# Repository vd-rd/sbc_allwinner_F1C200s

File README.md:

# Allwinner F1C200s SBC

This board embeds a SIP (single core 533MHz ARM926EJ-S with 64MB DDR) with AXP173 PMIC, IO headers and microSD/eMMC storage. The board is also compatible with the smaller F1C100s that only embedds 32MB DDR RAM.

Note: The uC has two SDIO controllers (SDIO0 - 4bit wide, SDIO1 - 1bit wide). SDIO0 is used for SDCard. To provide wireless networking, while not sacrificing a large amount of pins, a design decision was made to use ESP32 module to provide WiFi/BT capabilities connected via SPI bus, leveraging [ESP_HOSTED_NG](https://github.com/espressif/esp-hosted) as a solution.
## Board overview (draft):

[TBD]

## Board features

| Characteristic | Description |
| --- | --- |
| Dimensions | 60mm x 40mm |
| Processor | Allwinner F1C100s/F1C200s ARM926EJ-S @533MHz |
| Oscillators | 24MHz main clock |
| RAM | 32/64MB embedded DDR memory |
| Storage | microSD/eMMC |
| USB | 1 microUSB OTG |
| Supply | Power path between USB/Vin/Battery, 5V max |

## Notes and observations
[TBD]

## Resources
 - online viewer for schematic/layout (https://cadlab.io/project/23988).

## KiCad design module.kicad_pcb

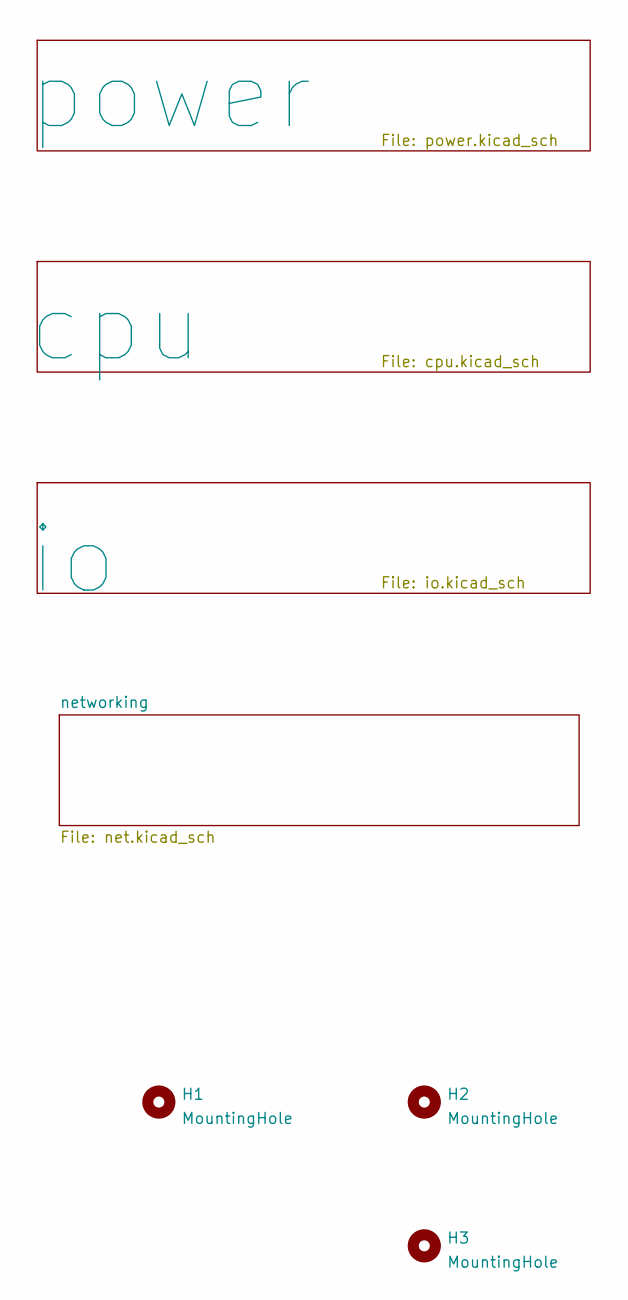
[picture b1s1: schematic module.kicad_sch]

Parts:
H1, H2, H3: MountingHole; MountingHole_2.7mm_M2.5

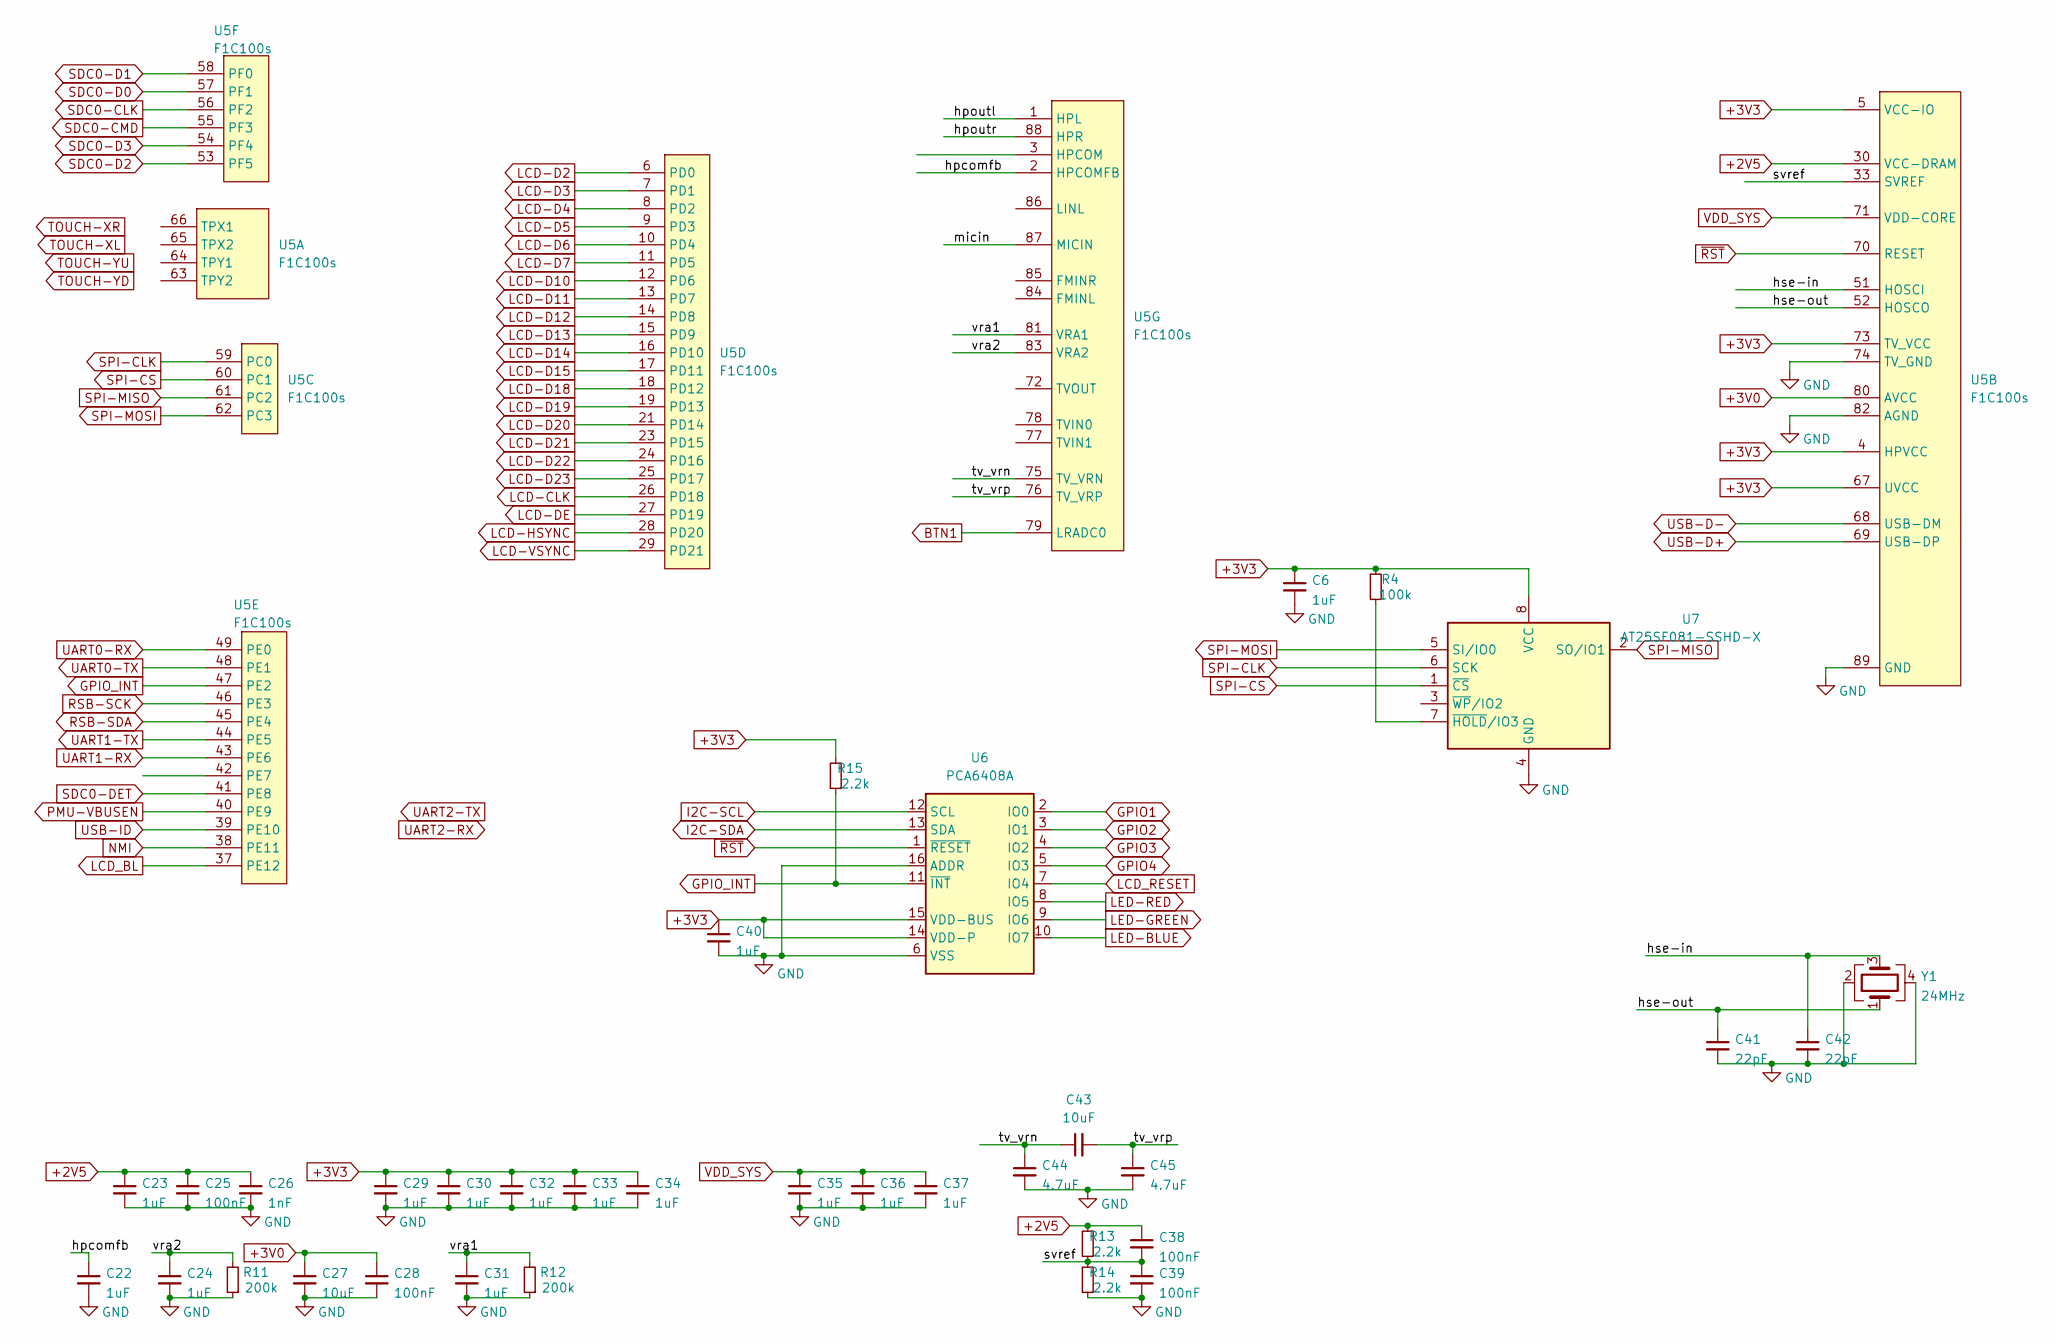
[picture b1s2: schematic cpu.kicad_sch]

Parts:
C6, C22, C23, C24, C29, C30, C31, C32, C33, C34, C35, C36, C37, C40: 1uF; C_0402_1005Metric
C25, C28, C38, C39: 100nF; C_0402_1005Metric
C26: 1nF; C_0402_1005Metric
C27, C43: 10uF; C_0603_1608Metric
C41, C42: 22pF; C_0402_1005Metric
C44, C45: 4.7uF; C_0603_1608Metric
R4: 100k; R_0402_1005Metric
R11, R12: 200k; R_0402_1005Metric
R13, R14, R15: 2.2k; R_0402_1005Metric
U5: F1C100s; QFN-88_EP_10x10_Pitch0.4mm
U6: PCA6408A; QFN-16-1EP_3x3mm_P0.5mm_EP1.7x1.7mm
U7: AT25SF081-SSHD-X; SOIC-8_3.9x4.9mm_P1.27mm
Y1: 24MHz; Crystal_SMD_3225-4Pin_3.2x2.5mm

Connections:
+2V5: C23.1, C25.1, C26.1, C38.1, R13.2, U5.30 (VCC-DRAM), U5.31 (VCC-DRAM), U5.32 (VCC-DRAM), U5.34 (VCC-DRAM), U5.36 (VCC-DRAM); also elsewhere on the board
+3V0: C27.1, C28.1, U5.80 (AVCC); also elsewhere on the board
+3V3: C6.1, C29.1, C30.1, C32.1, C33.1, C34.1, C40.1, R4.2, R15.2, U5.4 (HPVCC), U5.5 (VCC-IO), U5.20 (VCC-IO), U5.50 (VCC-IO), U5.67 (UVCC), U5.73 (TV_VCC), U6.14 (VDD-P), U6.15 (VDD-BUS), U7.8 (VCC); also elsewhere on the board
/cpu/hpcomfb: C22.1, U5.2 (HPCOMFB)
/cpu/hpoutl: U5.1 (HPL)
/cpu/hpoutr: U5.88 (HPR)
/cpu/hse-in: C42.1, U5.51 (HOSCI), Y1.3
/cpu/hse-out: C41.1, U5.52 (HOSCO), Y1.1
/cpu/micin: U5.87 (MICIN)
/cpu/svref: C38.2, C39.1, R13.1, R14.2, U5.33 (SVREF)
/cpu/tv_vrn: C43.1, C44.1, U5.75 (TV_VRN)
/cpu/tv_vrp: C43.2, C45.1, U5.76 (TV_VRP)
/cpu/vra1: C31.1, R12.2, U5.81 (VRA1)
/cpu/vra2: C24.1, R11.2, U5.83 (VRA2)
BTN1: U5.79 (LRADC0); also elsewhere on the board
GND: C6.2, C22.2, C23.2, C24.2, C25.2, C26.2, C27.2, C28.2, C29.2, C30.2, C31.2, C32.2, C33.2, C34.2, C35.2, C36.2, C37.2, C39.2, C40.2, C41.2, C42.2, C44.2, C45.2, R11.1, R12.1, R14.1, U5.74 (TV_GND), U5.82 (AGND), U5.89 (GND), U6.6 (VSS), U6.16 (ADDR), U7.4 (GND), Y1.2, Y1.4; also elsewhere on the board
GPIO1: U6.2 (IO0); also elsewhere on the board
GPIO2: U6.3 (IO1); also elsewhere on the board
GPIO3: U6.4 (IO2); also elsewhere on the board
GPIO4: U6.5 (IO3); also elsewhere on the board
GPIO_INT: R15.1, U5.47 (PE2), U6.11 (~INT)
I2C-SCL: U6.12 (SCL); also elsewhere on the board
I2C-SDA: U6.13 (SDA); also elsewhere on the board
LCD-CLK: U5.26 (PD18); also elsewhere on the board
LCD-D2: U5.6 (PD0); also elsewhere on the board
LCD-D3: U5.7 (PD1); also elsewhere on the board
LCD-D4: U5.8 (PD2); also elsewhere on the board
LCD-D5: U5.9 (PD3); also elsewhere on the board
LCD-D6: U5.10 (PD4); also elsewhere on the board
LCD-D7: U5.11 (PD5); also elsewhere on the board
LCD-D10: U5.12 (PD6); also elsewhere on the board
LCD-D11: U5.13 (PD7); also elsewhere on the board
LCD-D12: U5.14 (PD8); also elsewhere on the board
LCD-D13: U5.15 (PD9); also elsewhere on the board
LCD-D14: U5.16 (PD10); also elsewhere on the board
LCD-D15: U5.17 (PD11); also elsewhere on the board
LCD-D18: U5.18 (PD12); also elsewhere on the board
LCD-D19: U5.19 (PD13); also elsewhere on the board
LCD-D20: U5.21 (PD14); also elsewhere on the board
LCD-D21: U5.23 (PD15); also elsewhere on the board
LCD-D22: U5.24 (PD16); also elsewhere on the board
LCD-D23: U5.25 (PD17); also elsewhere on the board
LCD-DE: U5.27 (PD19); also elsewhere on the board
LCD-HSYNC: U5.28 (PD20); also elsewhere on the board
LCD-VSYNC: U5.29 (PD21); also elsewhere on the board
LCD_BL: U5.37 (PE12); also elsewhere on the board
LCD_RESET: U6.7 (IO4); also elsewhere on the board
LED-BLUE: U6.10 (IO7); also elsewhere on the board
LED-GREEN: U6.9 (IO6); also elsewhere on the board
LED-RED: U6.8 (IO5); also elsewhere on the board
NMI: U5.38 (PE11); also elsewhere on the board
unnamed: R4.1, U7.7 (~HOLD/IO3)
PMU-VBUSEN: U5.40 (PE9); also elsewhere on the board
RSB-SCK: U5.46 (PE3); also elsewhere on the board
RSB-SDA: U5.45 (PE4); also elsewhere on the board
SDC0-CLK: U5.56 (PF2); also elsewhere on the board
SDC0-CMD: U5.55 (PF3); also elsewhere on the board
SDC0-D0: U5.57 (PF1); also elsewhere on the board
SDC0-D1: U5.58 (PF0); also elsewhere on the board
SDC0-D2: U5.53 (PF5); also elsewhere on the board
SDC0-D3: U5.54 (PF4); also elsewhere on the board
SDC0-DET: U5.41 (PE8); also elsewhere on the board
SPI-CLK: U5.59 (PC0), U7.6 (SCK); also elsewhere on the board
SPI-CS: U5.60 (PC1), U7.1 (~CS); also elsewhere on the board
SPI-MISO: U5.61 (PC2), U7.2 (SO/IO1); also elsewhere on the board
SPI-MOSI: U5.62 (PC3), U7.5 (SI/IO0); also elsewhere on the board
UART0-RX: U5.49 (PE0); also elsewhere on the board
UART0-TX: U5.48 (PE1); also elsewhere on the board
UART1-RX: U5.43 (PE6); also elsewhere on the board
UART1-TX: U5.44 (PE5); also elsewhere on the board
USB-D+: U5.69 (USB-DP); also elsewhere on the board
USB-D-: U5.68 (USB-DM); also elsewhere on the board
USB-ID: U5.39 (PE10); also elsewhere on the board
VDD_SYS: C35.1, C36.1, C37.1, U5.22 (VDD-CORE), U5.35 (VDD-CORE), U5.71 (VDD-CORE); also elsewhere on the board
~RST: U5.70 (RESET), U6.1 (~RESET); also elsewhere on the board

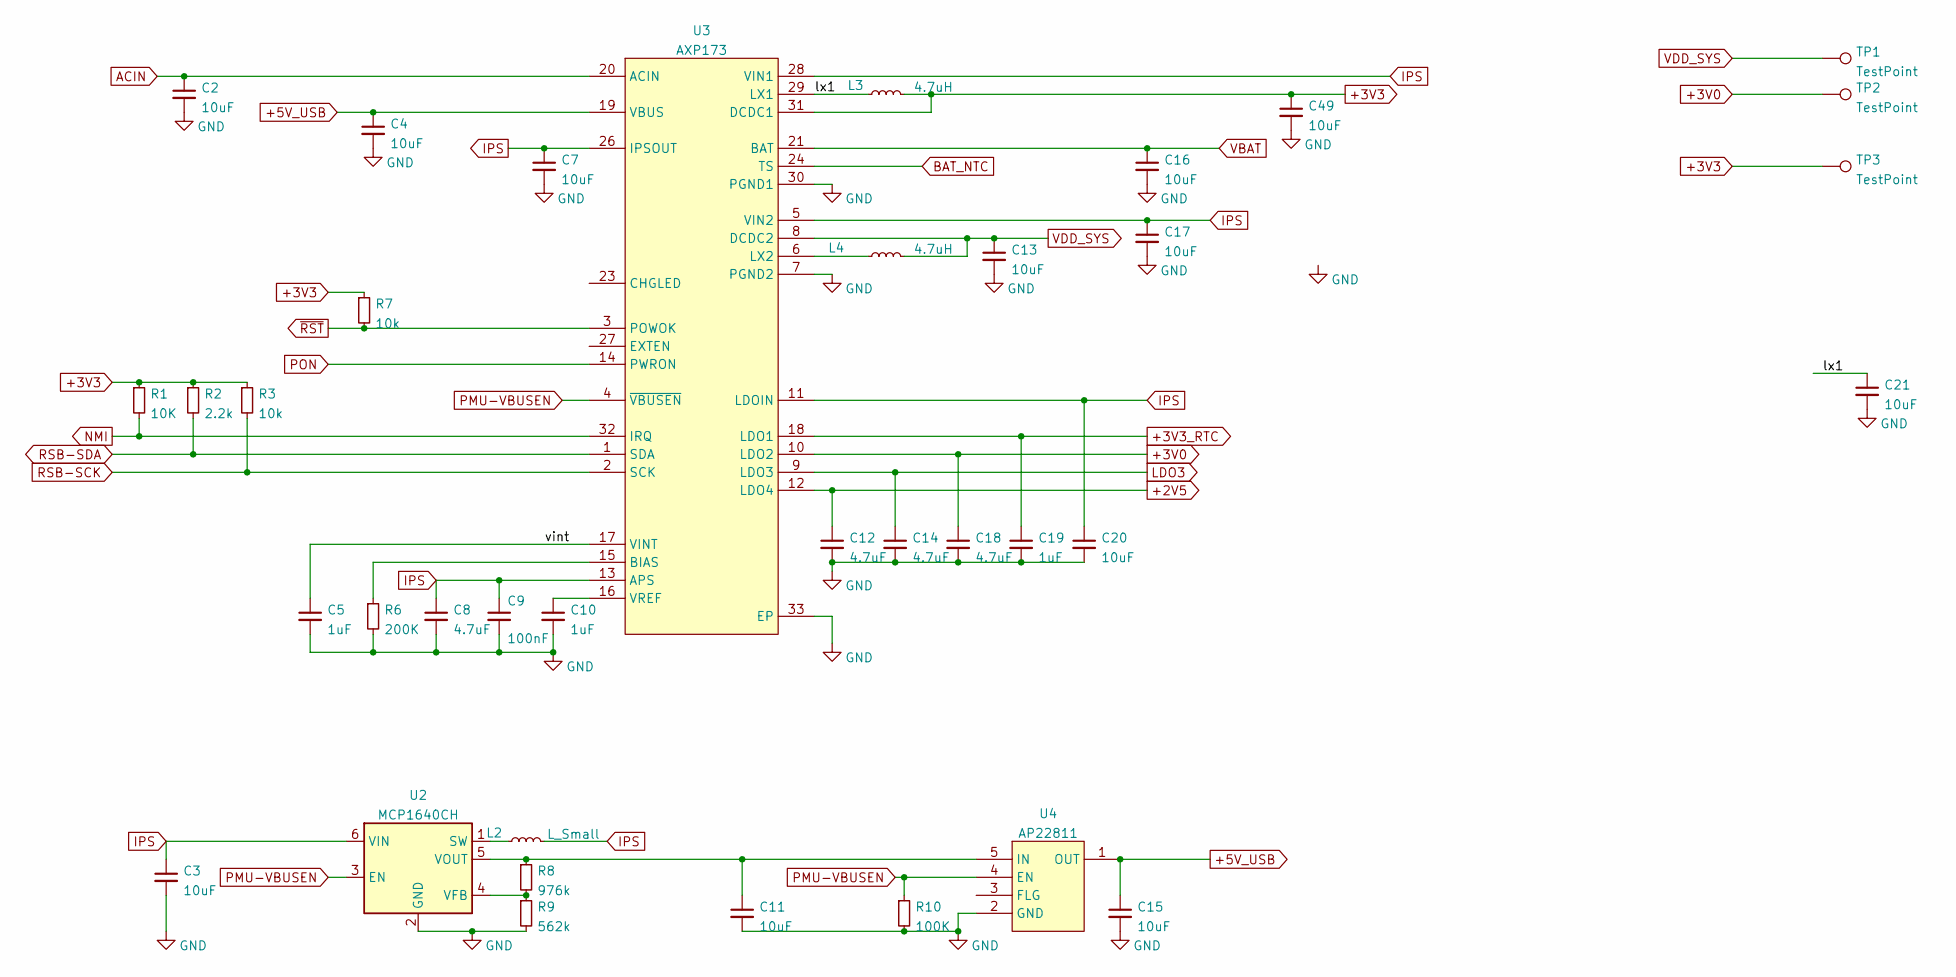
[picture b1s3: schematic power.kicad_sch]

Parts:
C2, C4, C7, C13, C16, C17, C20, C21, C49: 10uF; C_0603_1608Metric
C3, C11, C15: 10uF; C_0805_2012Metric
C5, C10, C19: 1uF; C_0402_1005Metric
C8, C12, C14, C18: 4.7uF; C_0603_1608Metric
C9: 100nF; C_0402_1005Metric
L2: L_Small; L_Wuerth_MAPI-2510
L3, L4: 4.7uH; L_Sunlord_SWPA252010S
R1: 10K; R_0402_1005Metric
R2: 2.2k; R_0402_1005Metric
R3, R7: 10k; R_0402_1005Metric
R6: 200K; R_0402_1005Metric
R8: 976k; R_0402_1005Metric
R9: 562k; R_0402_1005Metric
R10: 100K; R_0402_1005Metric
TP1, TP2, TP3: TestPoint; TestPoint_Pad_D1.0mm
U2: MCP1640CH; SOT-23-6
U3: AXP173; VQFN-32-1EP_5x5mm_P0.5mm_EP3.5x3.5mm_ThermalVias
U4: AP22811; SOT-23-5

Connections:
+2V5: C12.1, U3.12 (LDO4); also elsewhere on the board
+3V0: C18.1, TP2.1, U3.10 (LDO2); also elsewhere on the board
+3V3: C49.1, L3.2, R1.1, R2.1, R3.1, R7.1, TP3.1, U3.31 (DCDC1); also elsewhere on the board
+3V3_RTC: C19.1, U3.18 (LDO1)
+5V_USB: C4.1, C15.1, U3.19 (VBUS), U4.1 (OUT); also elsewhere on the board
/power/lx1: C21.1, L3.1, U3.29 (LX1)
/power/vint: C5.1, U3.17 (VINT)
ACIN: C2.1, U3.20 (ACIN); also elsewhere on the board
BAT_NTC: U3.24 (TS); also elsewhere on the board
GND: C2.2, C3.2, C4.2, C5.2, C7.2, C8.2, C9.2, C10.2, C11.2, C12.2, C13.2, C14.2, C15.2, C16.2, C17.2, C18.2, C19.2, C20.2, C21.2, C49.2, R6.2, R9.2, R10.2, U2.2 (GND), U3.7 (PGND2), U3.30 (PGND1), U3.33 (EP), U4.2 (GND); also elsewhere on the board
IPS: C3.1, C7.1, C8.1, C9.1, C17.1, C20.1, L2.2, U2.6 (VIN), U3.5 (VIN2), U3.11 (LDOIN), U3.13 (APS), U3.25 (IPSOUT), U3.26 (IPSOUT), U3.28 (VIN1)
LDO3: C14.1, U3.9 (LDO3); also elsewhere on the board
NMI: R1.2, U3.32 (IRQ); also elsewhere on the board
unnamed: L2.1, U2.1 (SW)
unnamed: R8.2, R9.1, U2.4 (VFB)
unnamed: C11.1, R8.1, U2.5 (VOUT), U4.5 (IN)
unnamed: R6.1, U3.15 (BIAS)
unnamed: L4.1, U3.6 (LX2)
unnamed: C10.1, U3.16 (VREF)
PMU-VBUSEN: R10.1, U2.3 (EN), U3.4 (~VBUSEN), U4.4 (EN); also elsewhere on the board
PON: U3.14 (PWRON); also elsewhere on the board
RSB-SCK: R3.2, U3.2 (SCK); also elsewhere on the board
RSB-SDA: R2.2, U3.1 (SDA); also elsewhere on the board
VBAT: C16.1, U3.21 (BAT), U3.22 (BAT); also elsewhere on the board
VDD_SYS: C13.1, L4.2, TP1.1, U3.8 (DCDC2); also elsewhere on the board
~RST: R7.2, U3.3 (POWOK); also elsewhere on the board

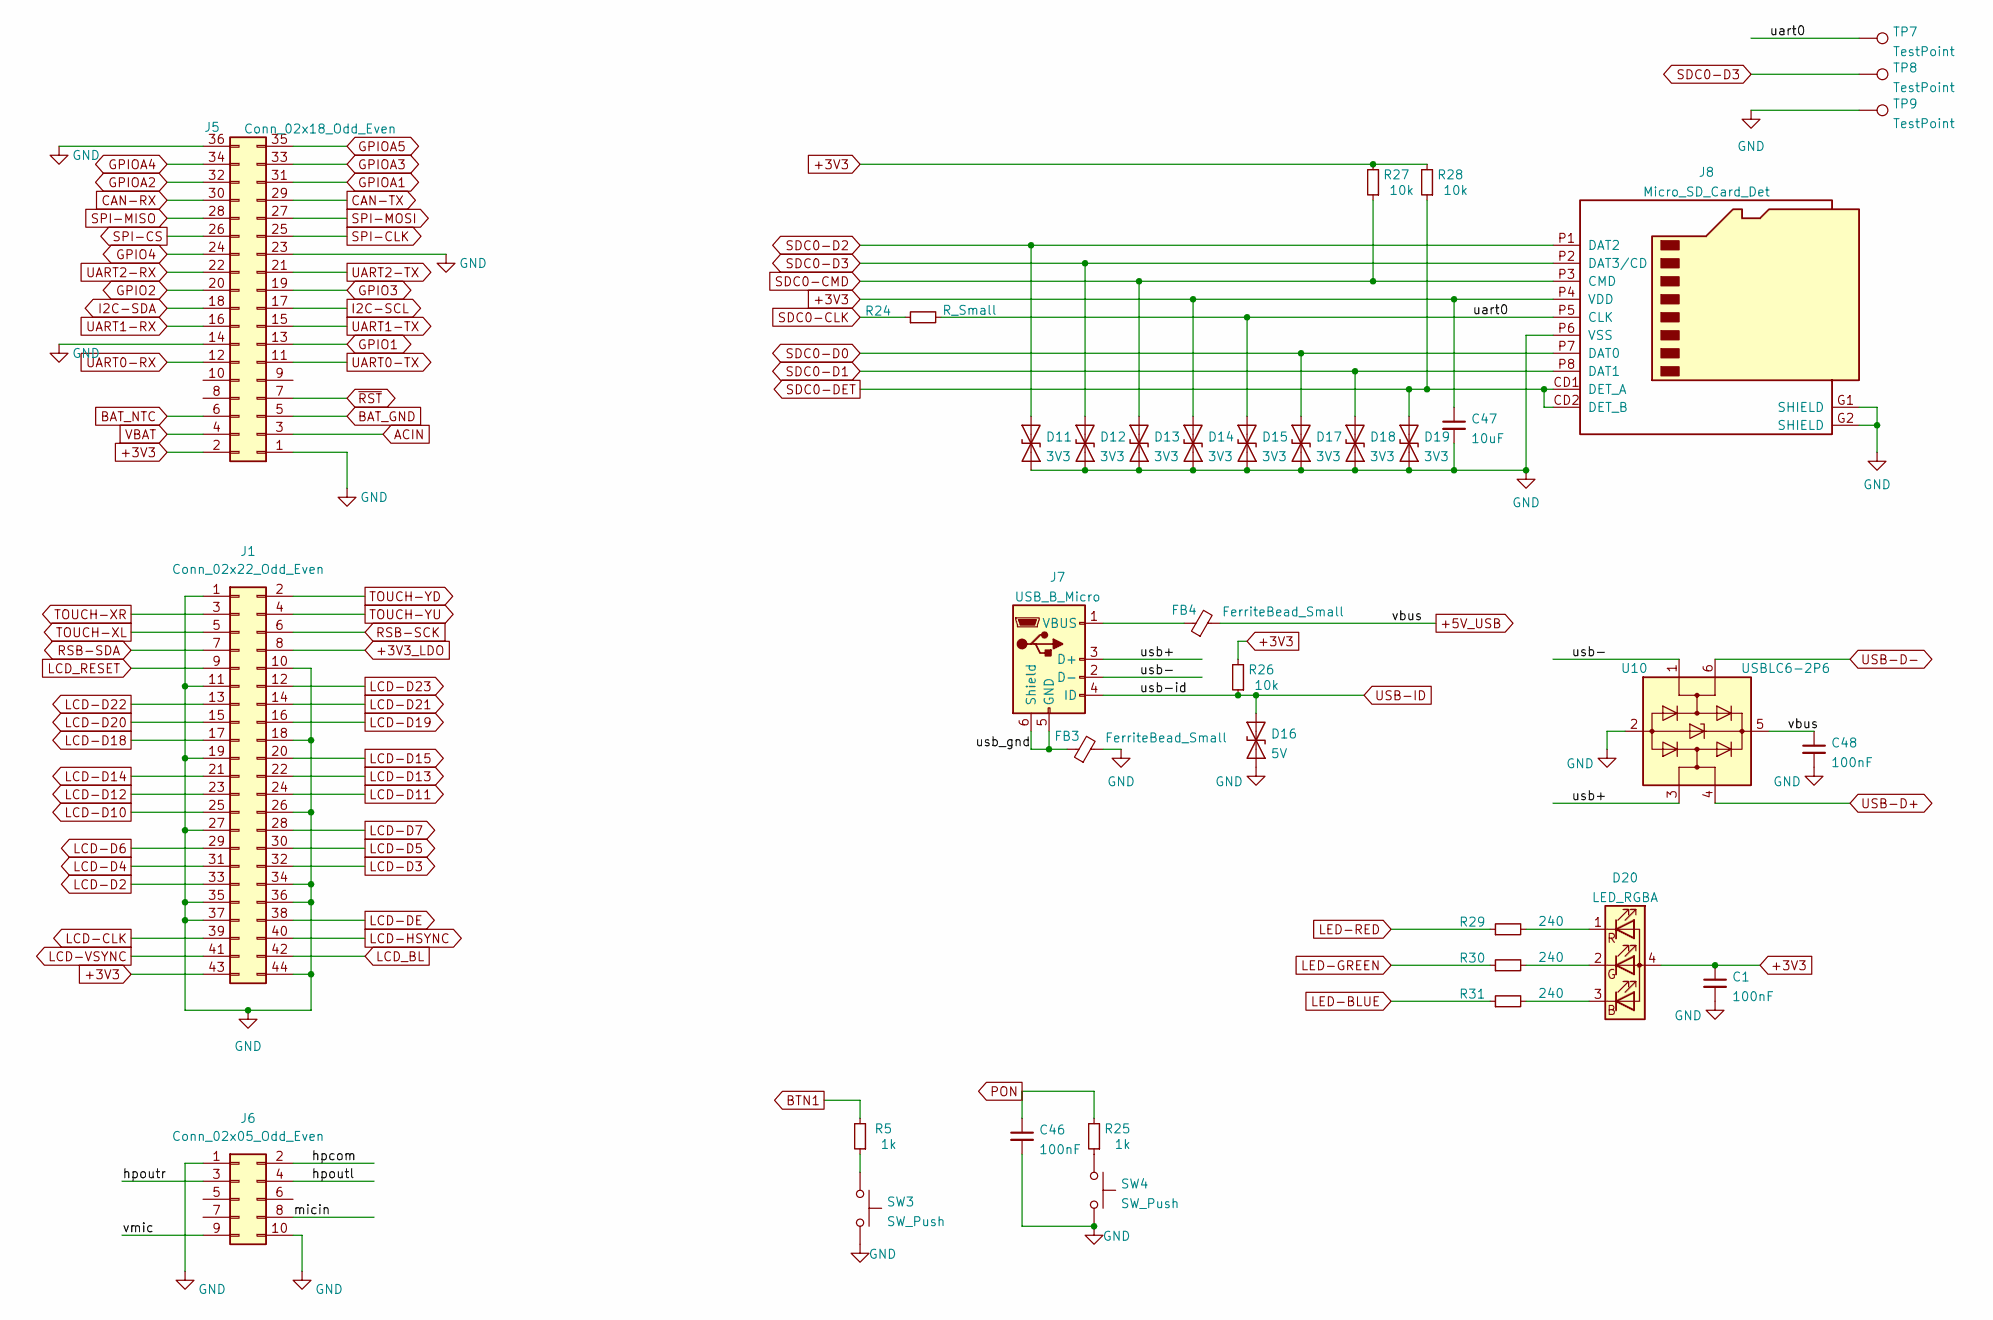
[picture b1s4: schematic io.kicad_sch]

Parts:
C1, C46, C48: 100nF; C_0402_1005Metric
C47: 10uF; C_0402_1005Metric
D11, D12, D13, D14, D15, D17, D18, D19: 3V3; D_SOD-923
D16: 5V; D_SOD-923
D20: LED_RGBA; rgb-1204
FB3, FB4: FerriteBead_Small; R_0603_1608Metric
J1: Conn_02x22_Odd_Even; PinHeader_2x22_P1.27mm_Vertical
J5: Conn_02x18_Odd_Even; PinHeader_2x18_P2.54mm_Vertical
J6: Conn_02x05_Odd_Even; PinHeader_2x05_P1.27mm_Vertical
J7: USB_B_Micro; USB_Micro-B_Amphenol_10103594-0001LF_Horizontal
J8: Micro_SD_Card_Det; MEM20610118800A
R5, R25: 1k; R_0402_1005Metric
R24: R_Small; R_0402_1005Metric
R26, R27, R28: 10k; R_0402_1005Metric
R29, R30, R31: 240; R_0402_1005Metric
SW3, SW4: SW_Push; SW_SPST_EVQP7C
TP7, TP8, TP9: TestPoint; TestPoint_Pad_D1.0mm
U10: USBLC6-2P6; SOT-666

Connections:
+3V3: C1.1, C47.1, D14.2 (A2), D20.4 (A), J1.43, J5.2, J8.P4 (VDD), R26.2, R27.2, R28.2; also elsewhere on the board
+3V3_LDO: J1.8
+5V_USB: C48.1, FB4.2, U10.5 (VBUS); also elsewhere on the board
/io/hpcom: J6.2
/io/hpoutl: J6.4
/io/hpoutr: J6.3
/io/micin: J6.8
/io/uart0: D15.2 (A2), J8.P5 (CLK), R24.2, TP7.1
/io/usb+: J7.3 (D+), U10.3 (I/O2)
/io/usb-: J7.2 (D-), U10.1 (I/O1)
/io/usb_gnd: FB3.1, J7.5 (GND), J7.6 (Shield)
/io/vmic: J6.9
ACIN: J5.3; also elsewhere on the board
BAT_GND: J5.5
BAT_NTC: J5.6; also elsewhere on the board
BTN1: R5.2; also elsewhere on the board
CAN-RX: J5.30
CAN-TX: J5.29
GND: C1.2, C46.2, C47.2, C48.2, D11.1 (A1), D12.1 (A1), D13.1 (A1), D14.1 (A1), D15.1 (A1), D16.1 (A1), D17.1 (A1), D18.1 (A1), D19.1 (A1), FB3.2, J1.1, J1.10, J1.11, J1.18, J1.19, J1.26, J1.27, J1.34, J1.35, J1.36, J1.37, J1.44, J5.1, J5.14, J5.23, J5.36, J6.1, J6.10, J8.G1 (SHIELD), J8.G2 (SHIELD), J8.P6 (VSS), SW3.2, SW4.2, TP9.1, U10.2 (GND); also elsewhere on the board
GPIO1: J5.13; also elsewhere on the board
GPIO2: J5.20; also elsewhere on the board
GPIO3: J5.19; also elsewhere on the board
GPIO4: J5.24; also elsewhere on the board
GPIOA1: J5.31
GPIOA2: J5.32
GPIOA3: J5.33
GPIOA4: J5.34
GPIOA5: J5.35
I2C-SCL: J5.17; also elsewhere on the board
I2C-SDA: J5.18; also elsewhere on the board
LCD-CLK: J1.39; also elsewhere on the board
LCD-D2: J1.33; also elsewhere on the board
LCD-D3: J1.32; also elsewhere on the board
LCD-D4: J1.31; also elsewhere on the board
LCD-D5: J1.30; also elsewhere on the board
LCD-D6: J1.29; also elsewhere on the board
LCD-D7: J1.28; also elsewhere on the board
LCD-D10: J1.25; also elsewhere on the board
LCD-D11: J1.24; also elsewhere on the board
LCD-D12: J1.23; also elsewhere on the board
LCD-D13: J1.22; also elsewhere on the board
LCD-D14: J1.21; also elsewhere on the board
LCD-D15: J1.20; also elsewhere on the board
LCD-D18: J1.17; also elsewhere on the board
LCD-D19: J1.16; also elsewhere on the board
LCD-D20: J1.15; also elsewhere on the board
LCD-D21: J1.14; also elsewhere on the board
LCD-D22: J1.13; also elsewhere on the board
LCD-D23: J1.12; also elsewhere on the board
LCD-DE: J1.38; also elsewhere on the board
LCD-HSYNC: J1.40; also elsewhere on the board
LCD-VSYNC: J1.41; also elsewhere on the board
LCD_BL: J1.42; also elsewhere on the board
LCD_RESET: J1.9; also elsewhere on the board
LED-BLUE: R31.1; also elsewhere on the board
LED-GREEN: R30.1; also elsewhere on the board
LED-RED: R29.1; also elsewhere on the board
unnamed: D20.3 (BK), R31.2
unnamed: D20.2 (GK), R30.2
unnamed: D20.1 (RK), R29.2
unnamed: FB4.1, J7.1 (VBUS)
unnamed: R5.1, SW3.1
unnamed: R25.1, SW4.1
PON: C46.1, R25.2; also elsewhere on the board
RSB-SCK: J1.6; also elsewhere on the board
RSB-SDA: J1.7; also elsewhere on the board
SDC0-CLK: R24.1; also elsewhere on the board
SDC0-CMD: D13.2 (A2), J8.P3 (CMD), R27.1; also elsewhere on the board
SDC0-D0: D17.2 (A2), J8.P7 (DAT0); also elsewhere on the board
SDC0-D1: D18.2 (A2), J8.P8 (DAT1); also elsewhere on the board
SDC0-D2: D11.2 (A2), J8.P1 (DAT2); also elsewhere on the board
SDC0-D3: D12.2 (A2), J8.P2 (DAT3/CD), TP8.1; also elsewhere on the board
SDC0-DET: D19.2 (A2), J8.CD1 (DET_A), J8.CD2 (DET_B), R28.1; also elsewhere on the board
SPI-CLK: J5.25; also elsewhere on the board
SPI-CS: J5.26; also elsewhere on the board
SPI-MISO: J5.28; also elsewhere on the board
SPI-MOSI: J5.27; also elsewhere on the board
TOUCH-XL: J1.5
TOUCH-XR: J1.3
TOUCH-YD: J1.2
TOUCH-YU: J1.4
UART0-RX: J5.12; also elsewhere on the board
UART0-TX: J5.11; also elsewhere on the board
UART1-RX: J5.16; also elsewhere on the board
UART1-TX: J5.15; also elsewhere on the board
UART2-RX: J5.22
UART2-TX: J5.21
USB-D+: U10.4 (I/O2); also elsewhere on the board
USB-D-: U10.6 (I/O1); also elsewhere on the board
USB-ID: D16.2 (A2), J7.4 (ID), R26.1; also elsewhere on the board
VBAT: J5.4; also elsewhere on the board
~RST: J5.7; also elsewhere on the board

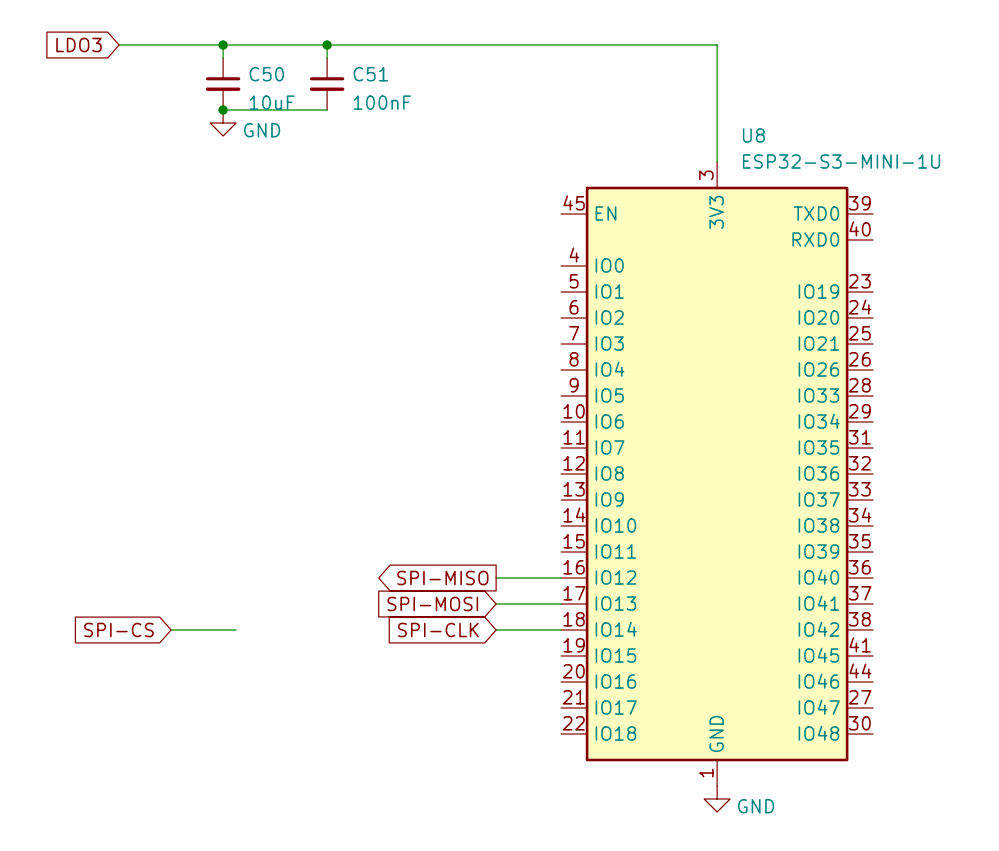
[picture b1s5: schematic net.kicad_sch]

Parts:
C50: 10uF; C_0603_1608Metric
C51: 100nF; C_0402_1005Metric
U8: ESP32-S3-MINI-1U; ESP32-S2-MINI-1U

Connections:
GND: C50.2, C51.2, U8.1 (GND), U8.2 (GND), U8.42 (GND), U8.43 (GND), U8.46 (GND), U8.47 (GND), U8.48 (GND), U8.49 (GND), U8.50 (GND), U8.51 (GND), U8.52 (GND), U8.53 (GND), U8.54 (GND), U8.55 (GND), U8.56 (GND), U8.57 (GND), U8.58 (GND), U8.59 (GND), U8.60 (GND), U8.61 (GND), U8.62 (GND), U8.63 (GND), U8.64 (GND), U8.65 (GND); also elsewhere on the board
LDO3: C50.1, C51.1, U8.3 (3V3); also elsewhere on the board
SPI-CLK: U8.18 (IO14); also elsewhere on the board
SPI-MISO: U8.16 (IO12); also elsewhere on the board
SPI-MOSI: U8.17 (IO13); also elsewhere on the board

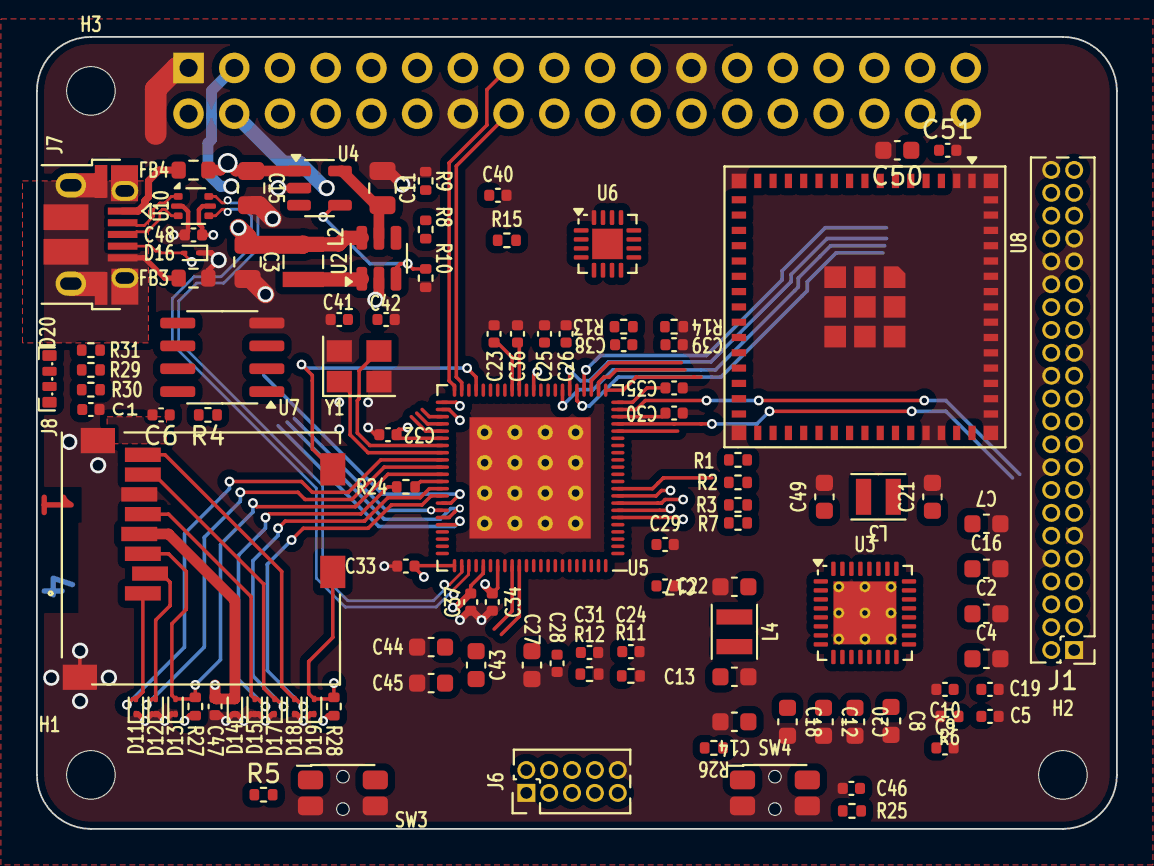
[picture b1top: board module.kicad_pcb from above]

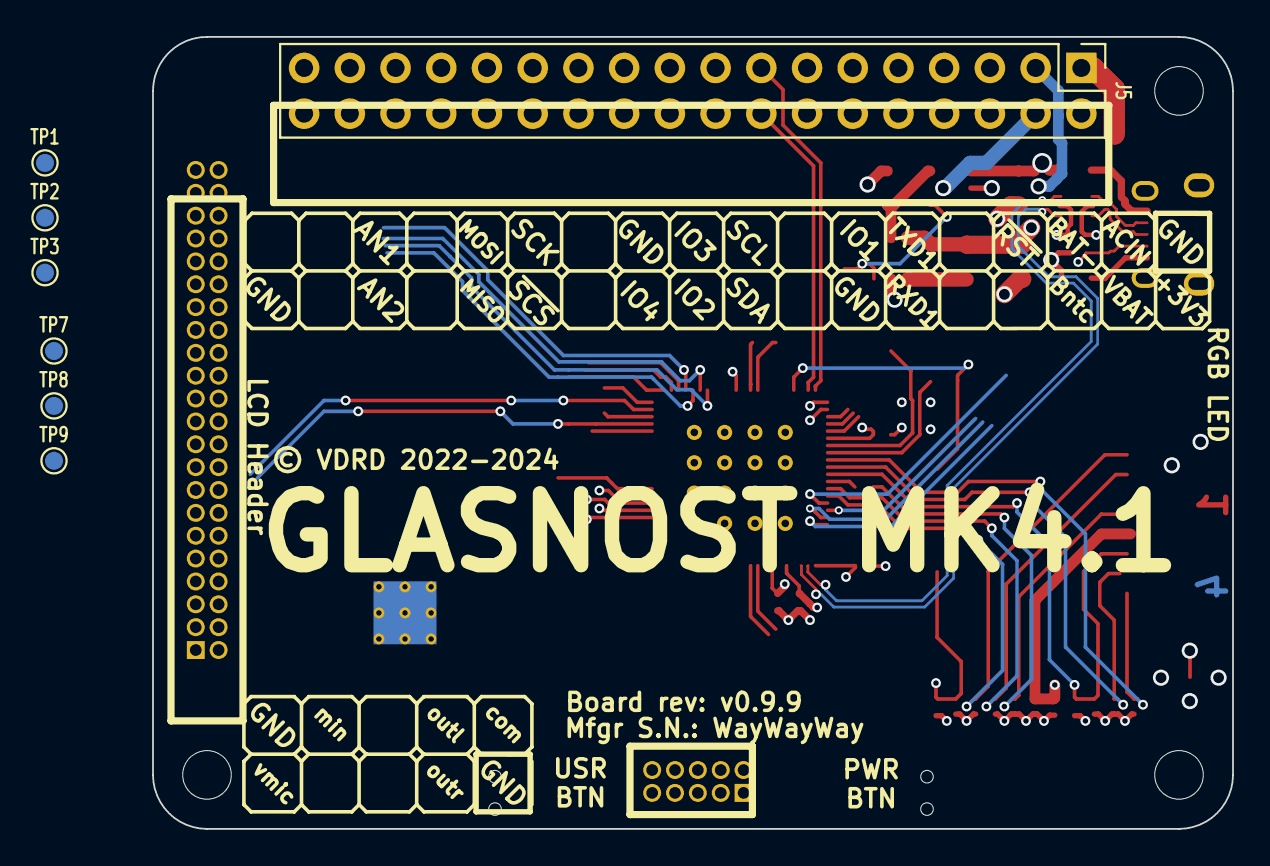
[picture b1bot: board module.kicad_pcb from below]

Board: 4 copper layers, 60.0 x 44.0 mm, 114 parts (7 on the bottom side), 98 nets.

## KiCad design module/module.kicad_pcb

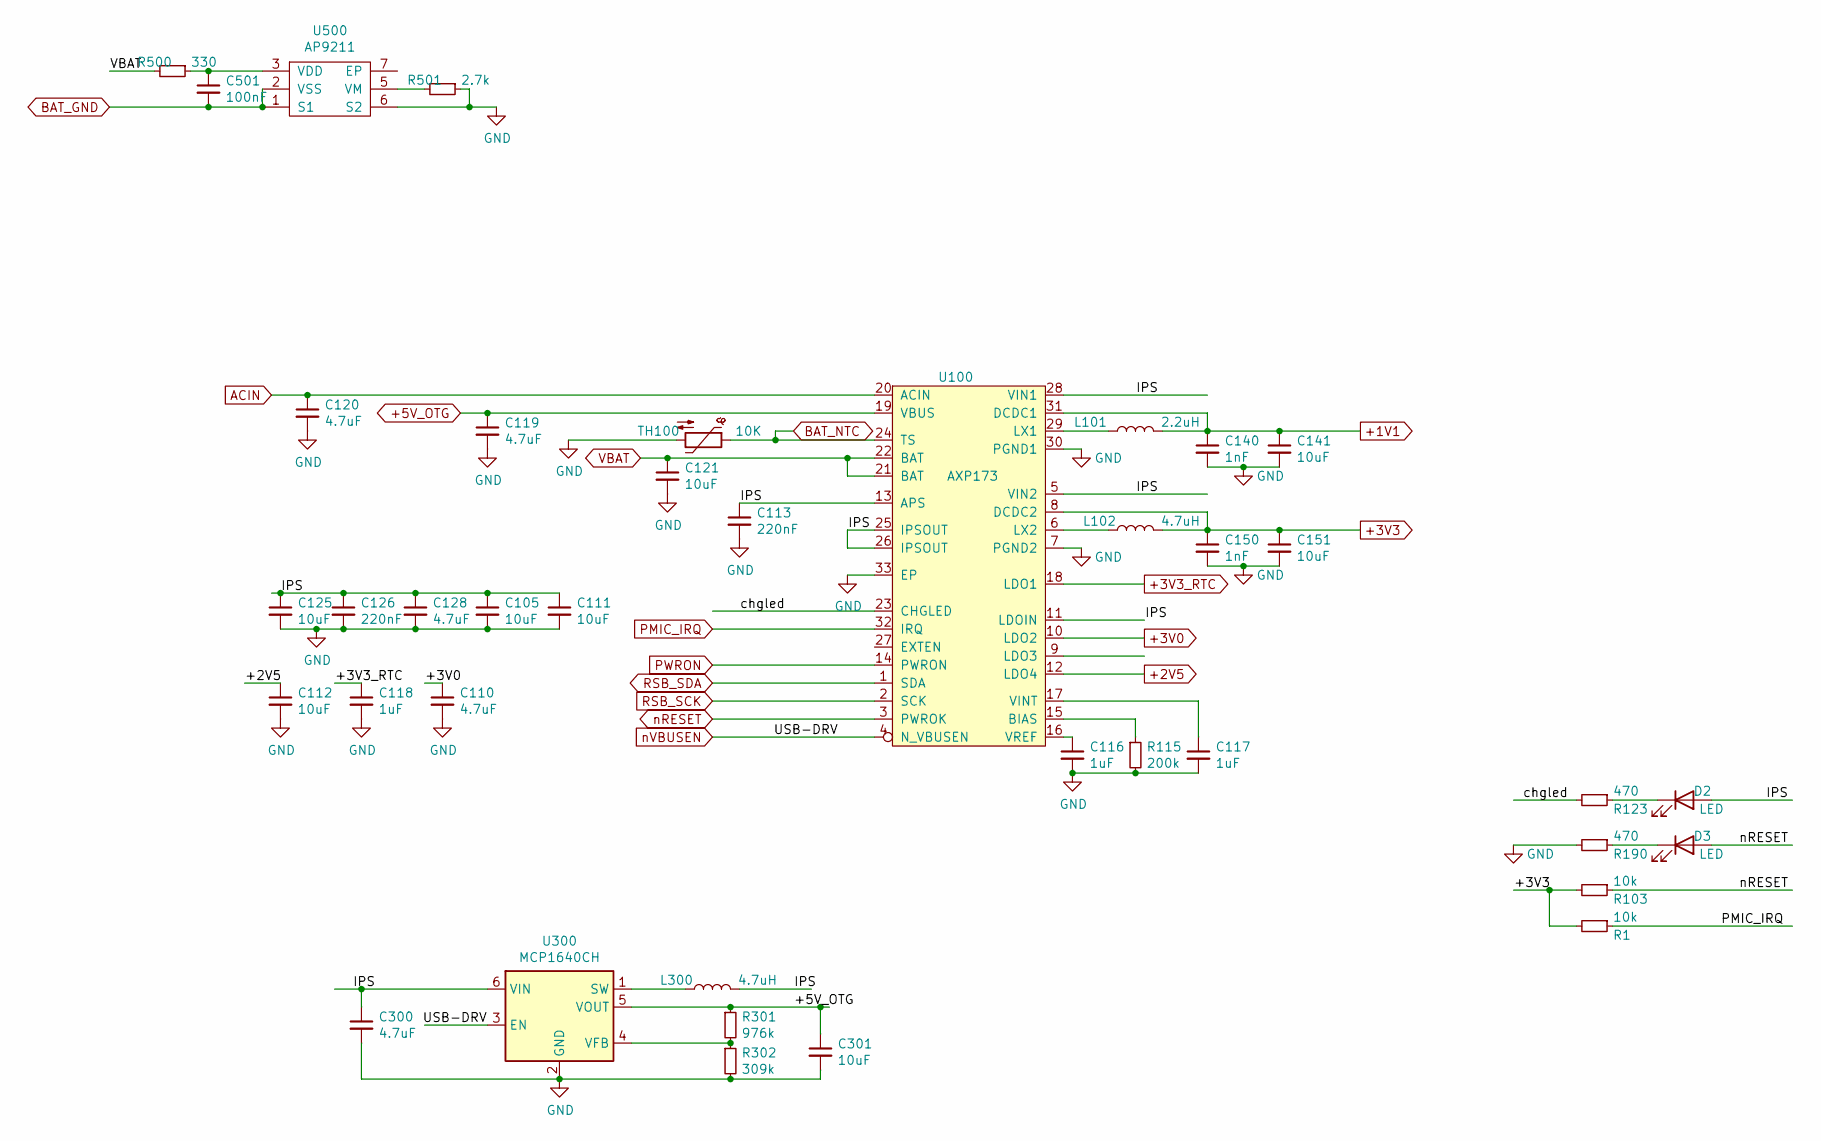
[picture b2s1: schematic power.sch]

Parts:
C105, C111, C112, C121, C125, C141, C151, C301: 10uF; C_0603_1608Metric
C110, C119, C120, C128, C300: 4.7uF; C_0603_1608Metric
C113, C126: 220nF; C_0402_1005Metric
C116, C117, C118: 1uF; C_0402_1005Metric
C140, C150: 1nF; C_0402_1005Metric
C501: 100nF; C_0402_1005Metric
D2, D3: LED; LED_0603_1608Metric
L101: 2.2uH; L_2520_power
L102, L300: 4.7uH; L_2520_power
R1, R103: 10k; R_0402_1005Metric; Tolerance 1%
R115: 200k; R_0402_1005Metric; Tolerance 1%
R123, R190: 470; R_0402_1005Metric; Tolerance 1%
R301: 976k; R_0402_1005Metric
R302: 309k; R_0402_1005Metric
R500: 330; R_0402_1005Metric; Tolerance 1%
R501: 2.7k; R_0402_1005Metric; Tolerance 1%
TH100: 10K; R_0402_1005Metric; Tolerance 1%
U100: AXP173; VQFN-32-1EP_5x5mm_P0.5mm_EP3.5x3.5mm_ThermalVias
U300: MCP1640CH; SOT-23-6
U500: AP9211; DFN-6-1EP_2.1X3.1mm_EP1.8X1.8mm

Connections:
+1V1: C140.1, C141.1, L101.2, U100.31 (DCDC1); also elsewhere on the board
+2V5: C112.1, U100.12 (LDO4); also elsewhere on the board
+3V0: C110.1, U100.10 (LDO2)
+3V3: C150.1, C151.1, L102.2, R1.2, R103.2, U100.8 (DCDC2); also elsewhere on the board
+3V3_RTC: C118.1, U100.18 (LDO1)
+5V_OTG: C119.1, C301.1, R301.1, U100.19 (VBUS), U300.5 (VOUT); also elsewhere on the board
/PMIC/IPS: C105.1, C111.1, C113.1, C125.1, C126.1, C128.1, C300.1, D2.2 (A), L300.2, U100.5 (VIN2), U100.11 (LDOIN), U100.13 (APS), U100.25 (IPSOUT), U100.26 (IPSOUT), U100.28 (VIN1), U300.6 (VIN)
/PMIC/chgled: R123.2, U100.23 (CHGLED)
ACIN: C120.1, U100.20 (ACIN); also elsewhere on the board
BAT_GND: C501.2, U500.1 (S1), U500.2 (VSS); also elsewhere on the board
BAT_NTC: TH100.1, U100.24 (TS); also elsewhere on the board
GND: C105.2, C110.2, C111.2, C112.2, C113.2, C116.2, C117.2, C118.2, C119.2, C120.2, C121.2, C125.2, C126.2, C128.2, C140.2, C141.2, C150.2, C151.2, C300.2, C301.2, R115.2, R190.2, R302.2, R501.1, TH100.2, U100.7 (PGND2), U100.30 (PGND1), U100.33 (EP), U300.2 (GND), U500.6 (S2); also elsewhere on the board
unnamed: C116.1, U100.16 (VREF)
unnamed: C117.1, U100.17 (VINT)
unnamed: C501.1, R500.1, U500.3 (VDD)
unnamed: D2.1 (K), R123.1
unnamed: D3.1 (K), R190.1
unnamed: L101.1, U100.29 (LX1)
unnamed: L102.1, U100.6 (LX2)
unnamed: L300.1, U300.1 (SW)
unnamed: R115.1, U100.15 (BIAS)
unnamed: R301.2, R302.1, U300.4 (VFB)
unnamed: R501.2, U500.5 (VM)
PWRON: U100.14 (PWRON); also elsewhere on the board
RSB_SCK: U100.2 (SCK); also elsewhere on the board
RSB_SDA: U100.1 (SDA); also elsewhere on the board
VBAT: C121.1, R500.2, U100.21 (BAT), U100.22 (BAT); also elsewhere on the board
nRESET: D3.2 (A), R103.1, U100.3 (PWROK); also elsewhere on the board
nVBUSEN: U100.4 (N_VBUSEN), U300.3 (EN); also elsewhere on the board

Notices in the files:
module.kicad_pcb:
© VDRD 2022-2024
